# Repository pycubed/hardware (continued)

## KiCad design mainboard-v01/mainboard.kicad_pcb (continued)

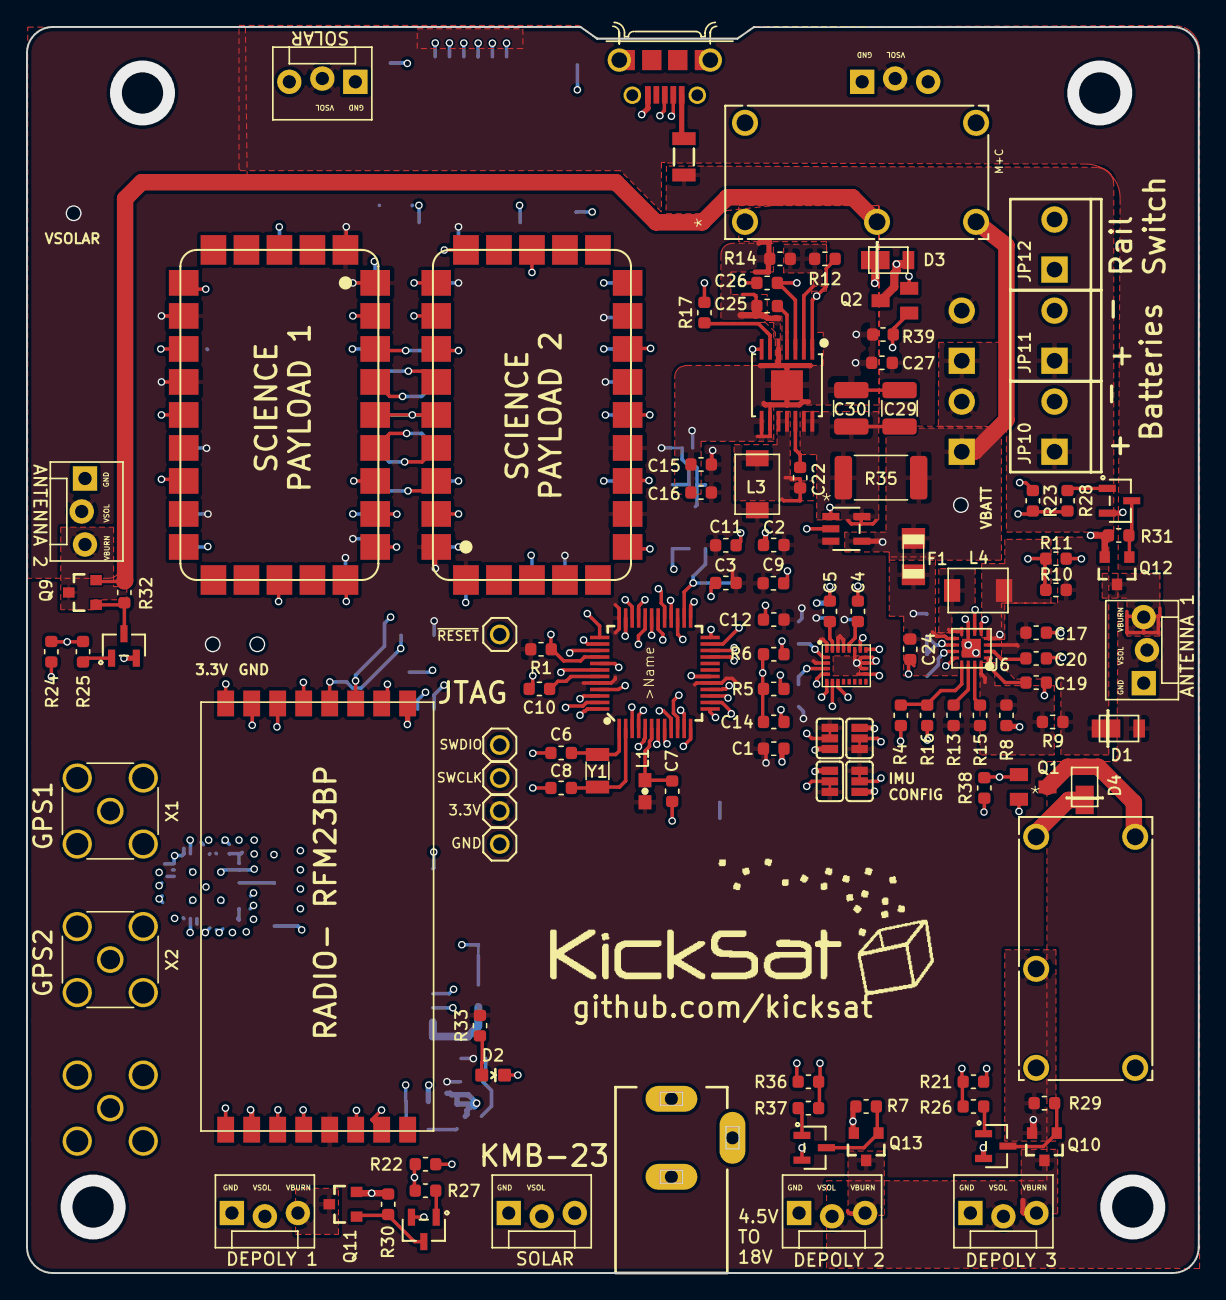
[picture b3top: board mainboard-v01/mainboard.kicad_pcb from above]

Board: 4 copper layers, 90.2 x 95.9 mm, 142 parts (0 on the bottom side), 104 nets.

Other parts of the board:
3.3V1: PINHD-1X1; 1X01
F2: 500mA; PTC-1206
GND1: PINHD-1X1; 1X01
L5, L5#2: KICKSAT_LOGO
Q9, Q10, Q11, Q12, Q13, Q16: IRLML5103; SOT23-3

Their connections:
3.3V: 3.3V1.1, Q16.2; also elsewhere on the board
/Burn Wires/VBURN1: Q9.3; also elsewhere on the board
/Burn Wires/VBURN2: Q12.3; also elsewhere on the board
/Burn Wires/VBURN3: Q11.3; also elsewhere on the board
/Burn Wires/VBURN4: Q10.3; also elsewhere on the board
/Burn Wires/VBURN5: Q13.3; also elsewhere on the board
/Burn Wires/VBURN_A_IN: Q9.2, Q12.2; also elsewhere on the board
/Burn Wires/VBURN_B_IN: Q10.2, Q11.2, Q13.2; also elsewhere on the board
/Connectors/VBATT_IN: F2.2; also elsewhere on the board
GND: GND1.1; also elsewhere on the board
GPS_PWR_IN: Q16.3; also elsewhere on the board
unnamed 82: Q16.1; also elsewhere on the board

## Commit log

2019-07-13 adding v01 hardware from KickSat and current mainboard-v02
2019-07-13 adding a gitignore file for KiCad back-up files
2019-07-13 adding v01 schematic pdf
2019-07-13 fixing bold font and adding schematic pdf of v02
2019-07-16 mainboard-v02 with RFM98PW
2019-07-28 adding adaptations directory
2019-07-28 adding flux capacitor
2019-07-28 making room for flux capacitor
2019-07-28 fixing flux capacitor layout
2019-07-28 adding pcb backups to the gitignore
2019-07-28 starting mainboard-v03
2019-07-28 schematic organizing
2019-07-28 clarifying "hardware"
2019-07-28 cleaning up schematic scheets
2019-07-28 adding interactive bom
2019-07-28 Set theme jekyll-theme-minimal
2019-07-28 adding interactive BOM for v01 and v02
2019-07-28 adding BOM links to readme
2019-07-31 adding PyCubed board image
2019-07-31 resizing board pic
2019-08-02 adding quick start link
2019-08-05 adding CC license
2019-12-01 mainboardv3 clean up
2019-12-01 adding mainboardv4 branch
2020-01-10 adding mainbaordv04 layout and BOM
2020-04-03 cleaned up v04
2020-05-27 adding battery board 🔋
2020-05-27 stovepiping battery board to master
2020-05-27 tweak image size
2020-05-27 adding disclaimer 😇
2020-08-31 adding battery board manufacturing zip for easy ordering
2021-03-08 added battery board v01b which disconnects corner thru-holes from GND and more DNP details
2021-07-22 updating pycubed resouces link
2021-08-13 adding v05 layout & schematics
2021-08-13 adding interactive BOM and updating readme
2021-09-05 adding mainboard change log
2021-09-18 adding more manufacturing outputs (placement, boms, etc)
2021-09-18 moving position files to their own directory
2021-09-21 tweaking one-shot values for reduced power consumption
2021-11-10 Update README.md
    https://forum.kicad.info/t/warning-avoid-all-links-to-kicad-pcb-org-use-kicad-org/31521
2022-01-16 updating to CC BY-SA and adding MIT for software
2022-01-16 adding license files
2022-01-16 unifying licenses
